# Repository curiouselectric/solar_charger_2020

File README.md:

# solar_charger_2020
This is a single cell 18650 Lithium Polymer battery charging circuit using one cell PV module.

Based upon the BQ24210 800mA, single-input, single cell Li-ion Solar battery charger from Texas Instruments:

https://www.ti.com/sitesearch/docs/universalsearch.tsp?searchTerm=BQ24210#q=BQ24210&t=everything&linkId=1

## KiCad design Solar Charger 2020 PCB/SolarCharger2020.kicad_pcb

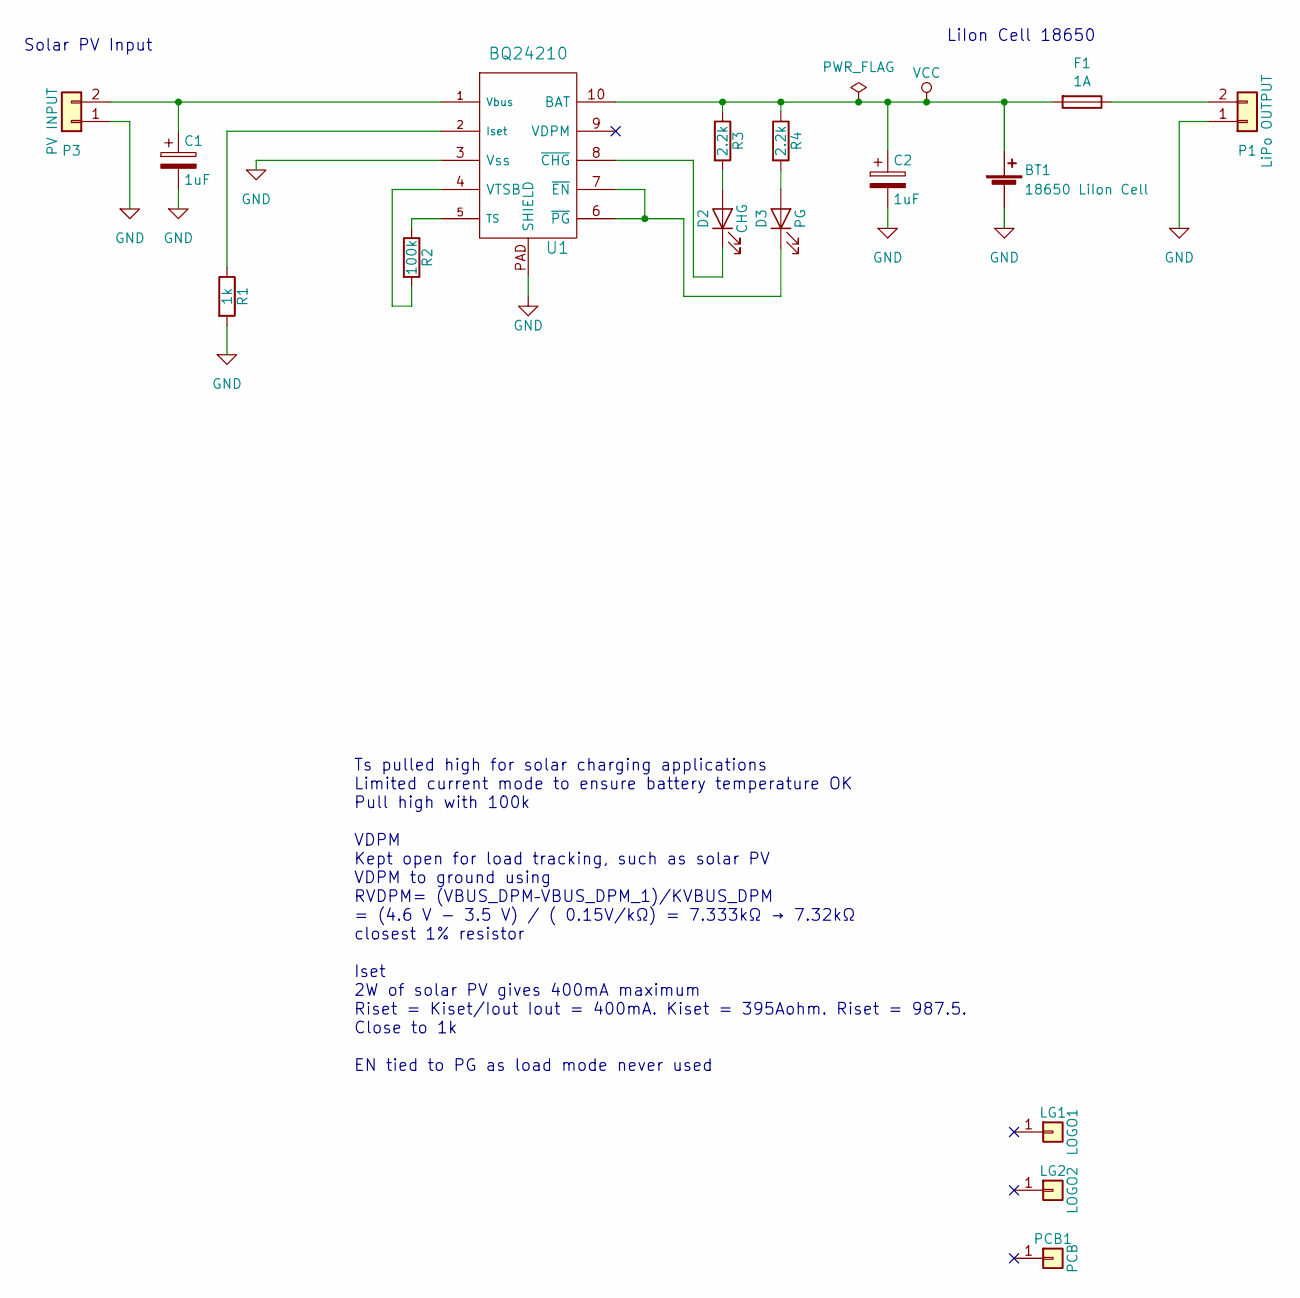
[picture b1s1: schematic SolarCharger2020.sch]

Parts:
BT1: 18650 LiIon Cell; TH_LiIon_Holder
C1, C2: 1uF; SM1206
D2: CHG; SM0805_LED
D3: PG; SM0805_LED
F1: 1A; SM_FSMD
LG1: LOGO1; 2019_011_16_CuriousElectricCompany_Logo_Round_Logo_No_words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
LG2: LOGO2; TCEC_Words_13mm
P1: LiPo OUTPUT; SIL_2_screw_+_JST_2mm
P3: PV INPUT; SIL_2_screw_+_JST_2mm
PCB1: PCB; PCB_SolarChargerPCB40x80
R1: 1k; SM0805
R2: 100k; SM0805
R3, R4: 2.2k; SM0805
U1: BQ24210; SM_WSON-10-2x3; Manufacturer Part No BQ24210

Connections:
GND: BT1.2 (-), C1.2, C2.2, P1.1, P3.1, R1.2, U1.3 (Vss), U1.PAD (SHIELD)
unnamed: C1.1, P3.2, U1.1 (Vbus)
unnamed: D2.1 (A), R3.2
unnamed: D2.2 (K), U1.8 (~CHG)
unnamed: D3.1 (A), R4.2
unnamed: D3.2 (K), U1.6 (~PG), U1.7 (~EN)
unnamed: F1.1, P1.2
unnamed: R1.1, U1.2 (Iset)
unnamed: R2.1, U1.5 (TS)
unnamed: R2.2, U1.4 (VTSB)
VCC: BT1.1 (+), C2.1, F1.2, R3.1, R4.1, U1.10 (BAT)

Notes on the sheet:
Solar PV Input
LiIon Cell 18650
Ts pulled high for solar charging applications Limited current mode to ensure battery temperature OK Pull high with 100k VDPM Kept open for load tracking, such as solar PV VDPM to ground using RVDPM= (VBUS_DPM–VBUS_DPM_1)/KVBUS_DPM = (4.6 V - 3.5 V) / ( 0.15V/kΩ) = 7.333kΩ → 7.32kΩ closest 1% resis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

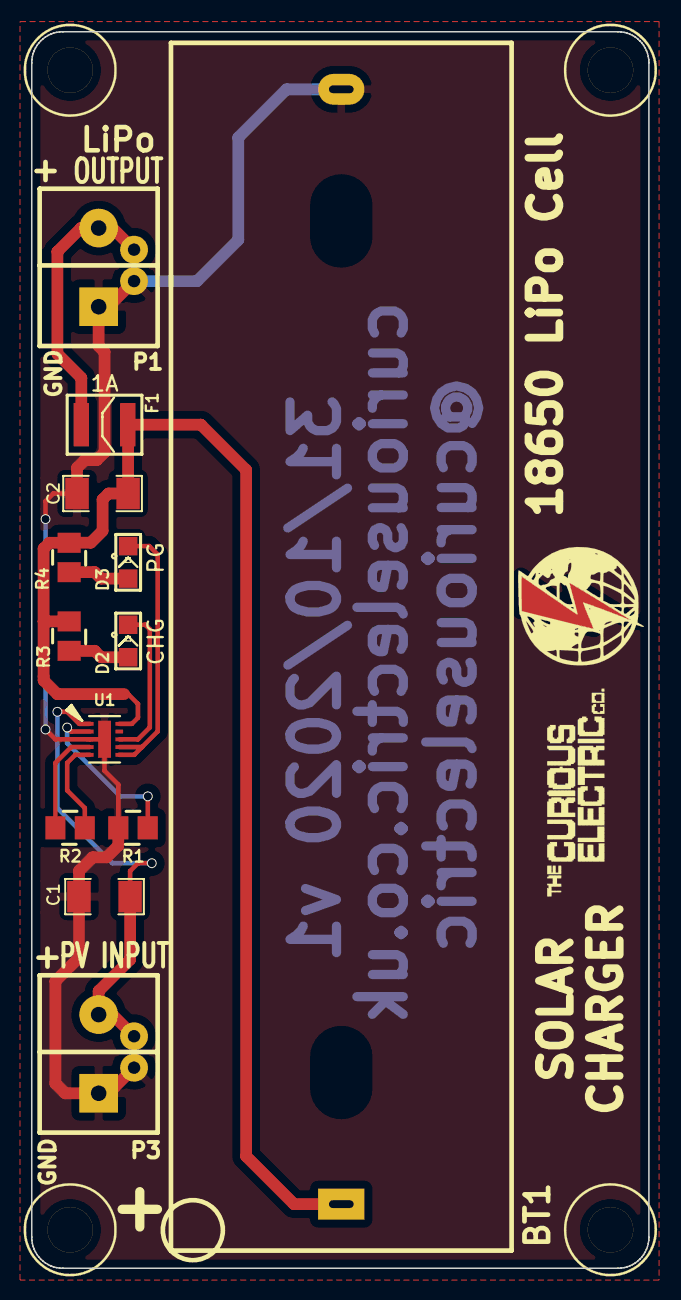
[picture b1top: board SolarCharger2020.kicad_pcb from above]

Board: 2 copper layers, 39.9 x 79.9 mm, 16 parts (1 on the bottom side), 11 nets.

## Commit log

2020-11-21 Full upload of PCB files and instructions
2020-11-21 Small update
2020-11-21 Update fp-info-cache
2020-12-17 Updated instructions
2020-12-17 Small instruction update
2020-12-18 update of photos
